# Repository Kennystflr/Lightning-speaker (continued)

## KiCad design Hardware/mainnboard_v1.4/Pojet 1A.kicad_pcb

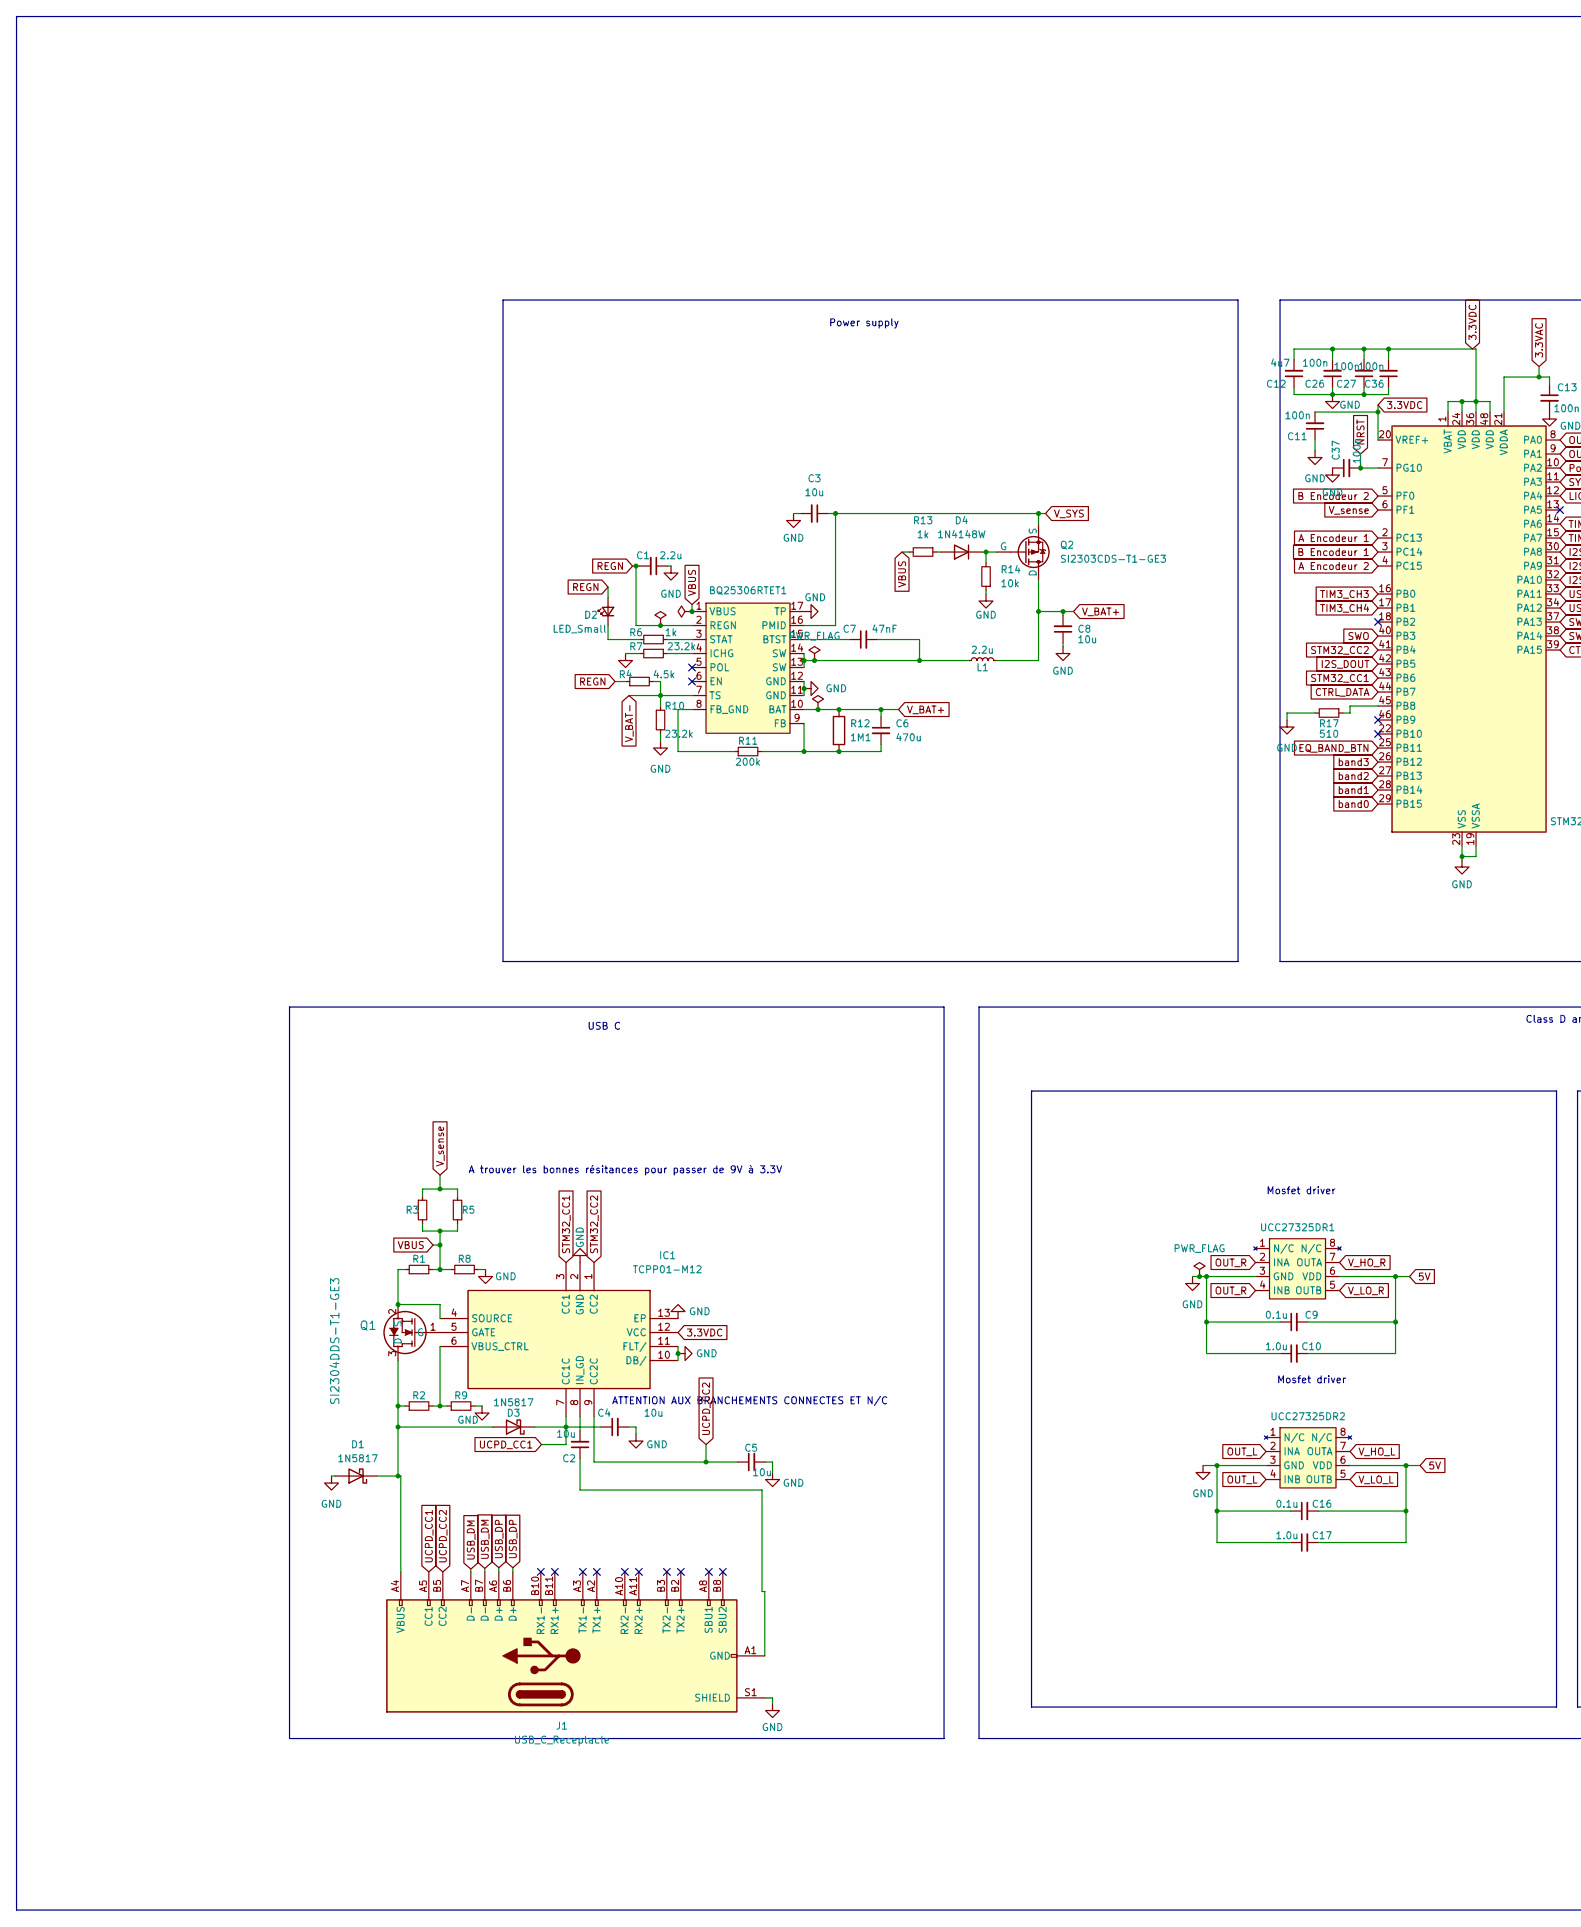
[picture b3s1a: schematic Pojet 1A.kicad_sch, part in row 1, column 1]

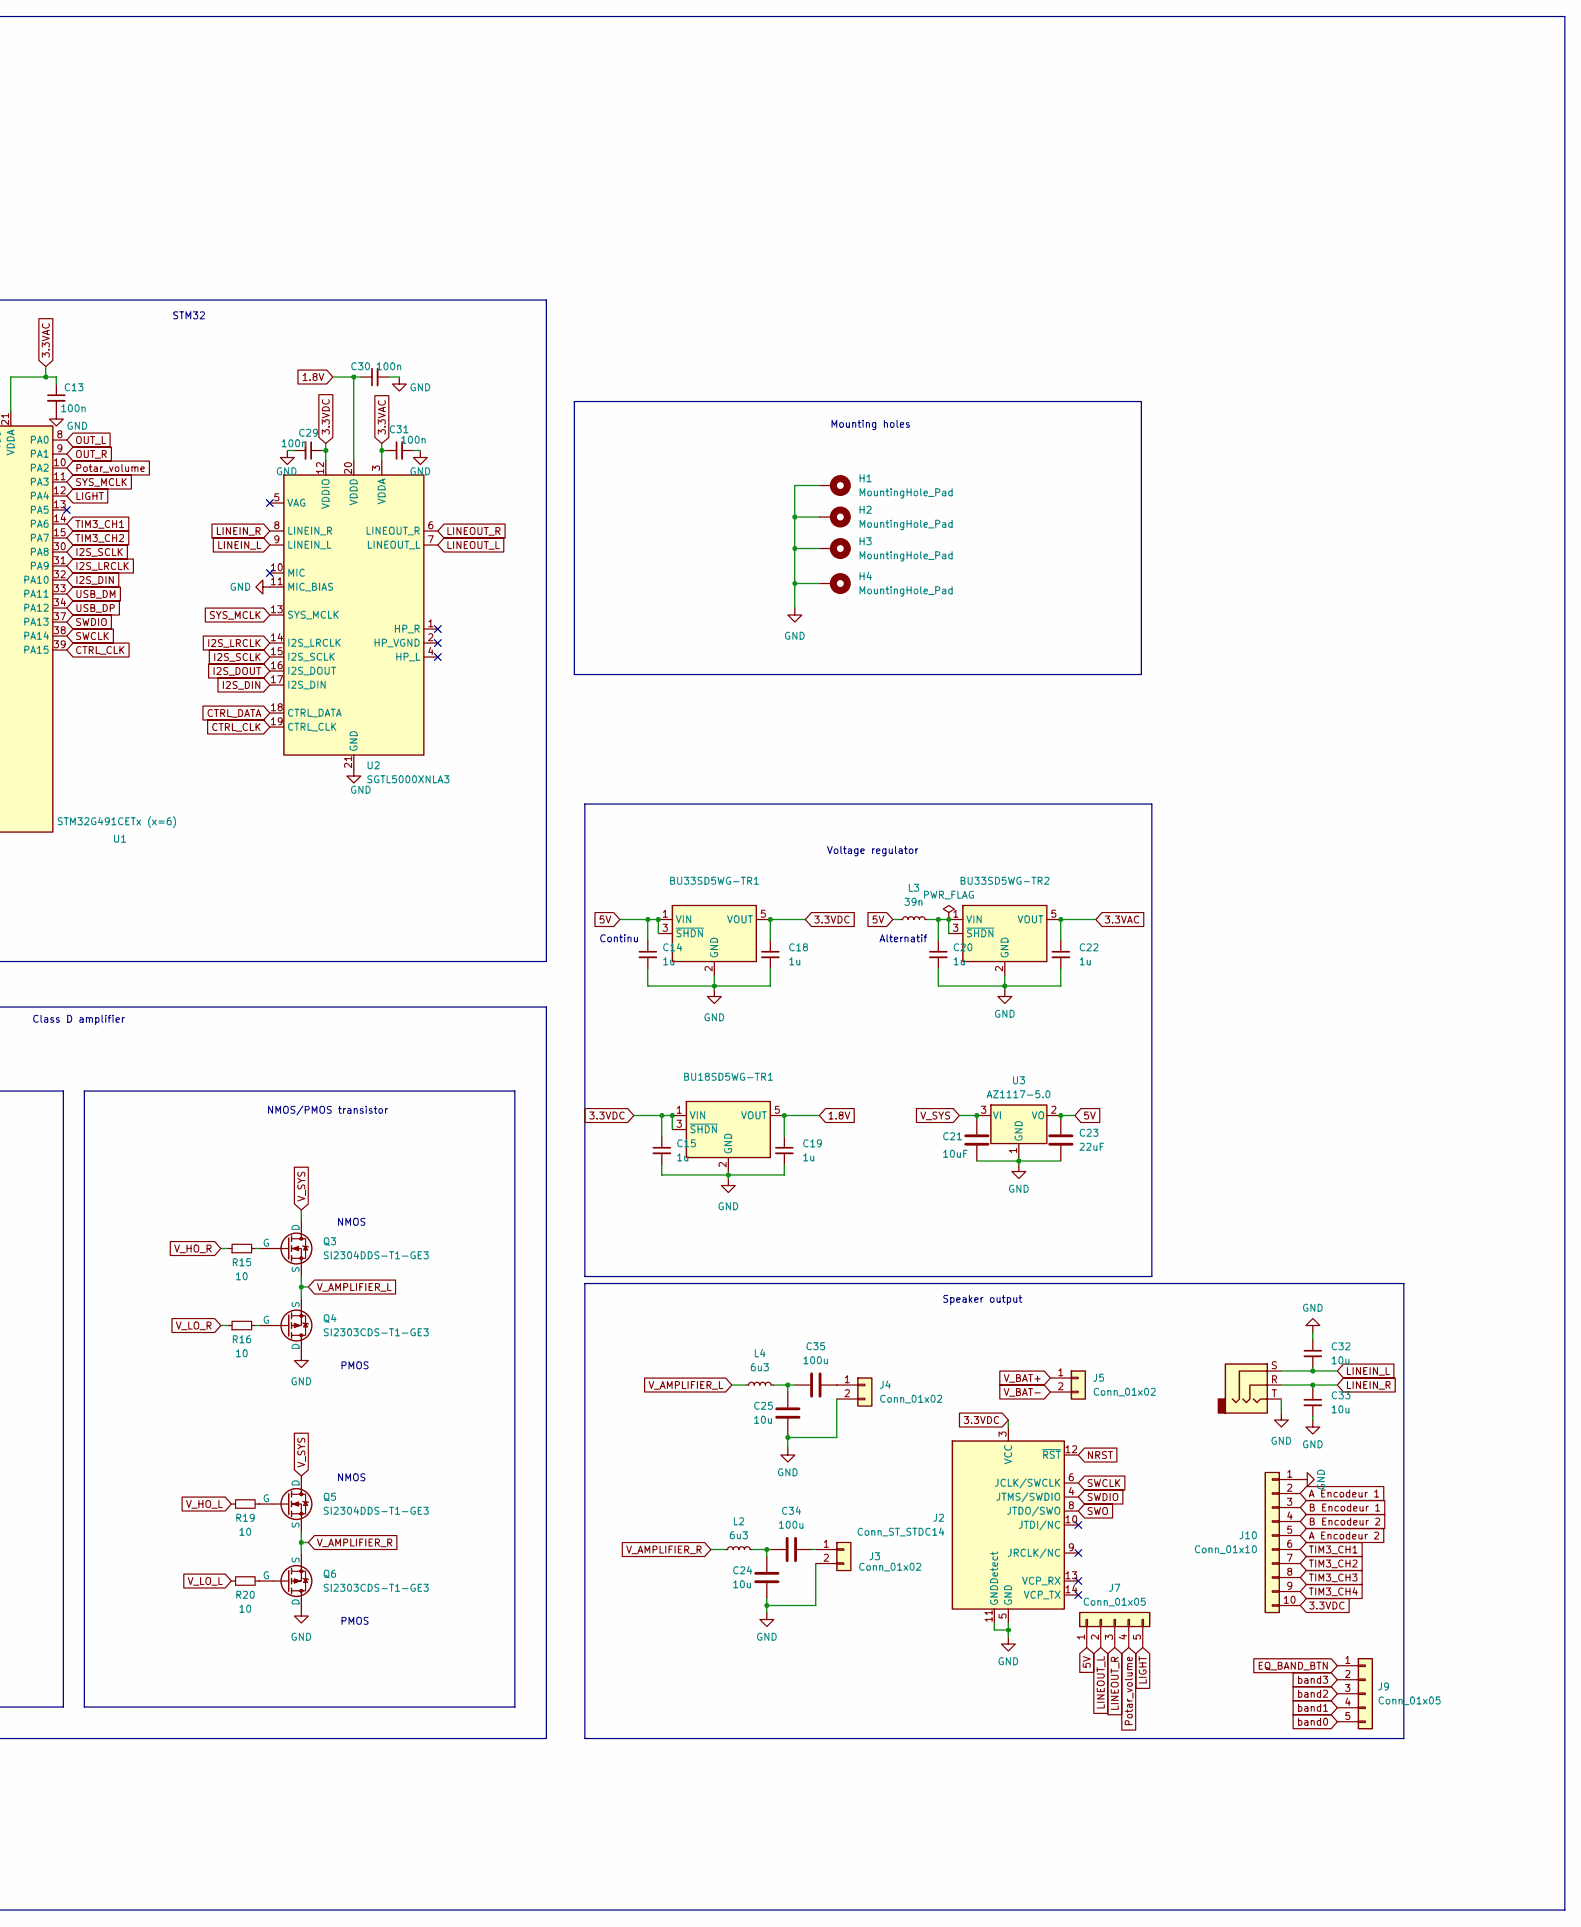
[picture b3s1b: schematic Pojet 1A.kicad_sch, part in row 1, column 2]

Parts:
BQ25306RTET1: WQFN-16-1EP_3x3mm_P0.5mm_EP1.75x1.75mm
BU18SD5WG-TR1, BU33SD5WG-TR1, BU33SD5WG-TR2: LM1117DT-3.3; SOT-23-5
C1: 2.2u; C_0805_2012Metric_Pad1.18x1.45mm_HandSolder
C2, C3, C4, C5, C8, C24, C25, C32, C33: 10u; C_0805_2012Metric_Pad1.18x1.45mm_HandSolder
C6: 470u; C_0805_2012Metric_Pad1.18x1.45mm_HandSolder
C7: 47nF; C_0805_2012Metric_Pad1.18x1.45mm_HandSolder
C9, C16: 0.1u; C_0805_2012Metric_Pad1.18x1.45mm_HandSolder
C10, C17: 1.0u; C_0805_2012Metric_Pad1.18x1.45mm_HandSolder
C11, C13, C26, C27, C29, C30, C31, C36, C37: 100n; C_0805_2012Metric_Pad1.18x1.45mm_HandSolder
C12: 4u7; C_0805_2012Metric_Pad1.18x1.45mm_HandSolder
C14, C15, C18, C19, C20, C22: 1u; C_0805_2012Metric_Pad1.18x1.45mm_HandSolder
C21: 10uF; C_0805_2012Metric_Pad1.18x1.45mm_HandSolder
C23: 22uF; C_0805_2012Metric_Pad1.18x1.45mm_HandSolder
C34, C35: 100u; C_Radial_D5.0mm_H11.0mm_P2.00mm
D1, D3: 1N5817; D_DO-41_SOD81_P10.16mm_Horizontal
D2: LED_Small; LED_D10.0mm
D4: 1N4148W; D_SOD-123
H1, H2, H3, H4: MountingHole_Pad; MountingHole_3.2mm_M3_DIN965_Pad
IC1: TCPP01-M12; LQFN-12-1EP_2x2mm_P0.5mm_EP0.7x0.7mm; Manufacturer_Part_Number TCPP01-M12; Mouser Part Number 511-TCPP01-M12
J1: USB_C_Receptacle; USB_C_Receptacle_GCT_USB4115-03-C
J2: Conn_ST_STDC14; PinHeader_2x07_P1.27mm_Vertical_SMD
J3, J4, J5: Conn_01x02; JST_XH_B2B-XH-A_1x02_P2.50mm_Vertical
J7, J9: Conn_01x05; PinHeader_1x05_P2.54mm_Vertical
J8: AudioJack3; Jack_6.35mm_Neutrik_NJ3FD-V_Vertical
J10: Conn_01x10; PinHeader_1x10_P2.54mm_Vertical
L1: 2.2u; L_0805_2012Metric_Pad1.05x1.20mm_HandSolder
L2, L4: 6u3; L_Vishay_IFSC-1515AH_4x4x1.8mm
L3: 39n; L_0603_1608Metric_Pad1.05x0.95mm_HandSolder
Q1, Q3, Q5: SI2304DDS-T1-GE3; SOT-23
Q2, Q4, Q6: SI2303CDS-T1-GE3; SOT-23
R1, R2, R3, R5, R8, R9: R_0603_1608Metric_Pad0.98x0.95mm_HandSolder
R4: 4.5k; R_0603_1608Metric_Pad0.98x0.95mm_HandSolder
R6, R13: 1k; R_0603_1608Metric_Pad0.98x0.95mm_HandSolder
R7, R10: 23.2k; R_0603_1608Metric_Pad0.98x0.95mm_HandSolder
R11: 200k; R_0603_1608Metric_Pad0.98x0.95mm_HandSolder
R12: 1M1; R_0603_1608Metric_Pad0.98x0.95mm_HandSolder
R14: 10k; R_0603_1608Metric_Pad0.98x0.95mm_HandSolder
R15, R16, R19, R20: 10; R_0603_1608Metric_Pad0.98x0.95mm_HandSolder
R17: 510; R_0603_1608Metric_Pad0.98x0.95mm_HandSolder
U1: STM32G491CETx (x=6); LQFP-48_7x7mm_P0.5mm
U2: SGTL5000XNLA3; QFN-20-1EP_3x3mm_P0.4mm_EP1.65x1.65mm
U3: AZ1117-5.0; SOT-223-3_TabPin2
UCC27325DR1, UCC27325DR2: SOIC-8_3.9x4.9mm_P1.27mm

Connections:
1.8V: BU18SD5WG-TR1.5 (VOUT), C19.1, C30.1, U2.20 (VDDD)
3.3VAC: BU33SD5WG-TR2.5 (VOUT), C13.1, C22.1, C31.1, U1.21 (VDDA), U2.3 (VDDA)
3.3VDC: BU18SD5WG-TR1.1 (VIN), BU18SD5WG-TR1.3 (~SHDN), BU33SD5WG-TR1.5 (VOUT), C11.2, C12.2, C15.1, C18.1, C26.2, C27.2, C29.1, C36.2, IC1.12 (VCC), J2.3 (VCC), J10.10, U1.1 (VBAT), U1.20 (VREF+), U1.24 (VDD), U1.36 (VDD), U1.48 (VDD), U2.12 (VDDIO)
5V: BU33SD5WG-TR1.1 (VIN), BU33SD5WG-TR1.3 (~SHDN), C9.2, C10.2, C14.1, C16.2, C17.2, C23.1, J7.1, L3.1, U3.2 (VO), UCC27325DR1.6 (VDD), UCC27325DR2.6 (VDD)
A Encodeur 1: J10.2, U1.2 (PC13)
A Encodeur 2: J10.5, U1.4 (PC15)
B Encodeur 1: J10.3, U1.3 (PC14)
B Encodeur 2: J10.4, U1.5 (PF0)
CTRL_CLK: U1.39 (PA15), U2.19 (CTRL_CLK)
CTRL_DATA: U1.44 (PB7), U2.18 (CTRL_DATA)
EQ_BAND_BTN: J9.1, U1.25 (PB11)
GND: BQ25306RTET1.11 (GND), BQ25306RTET1.12 (GND), BQ25306RTET1.17 (TP), BU18SD5WG-TR1.2 (GND), BU33SD5WG-TR1.2 (GND), BU33SD5WG-TR2.2 (GND), C1.1, C3.2, C4.2, C5.2, C8.1, C9.1, C10.1, C11.1, C12.1, C13.2, C14.2, C15.2, C16.1, C17.1, C18.2, C19.2, C20.2, C21.2, C22.2, C23.2, C24.2, C25.2, C26.1, C27.1, C29.2, C30.2, C31.2, C32.1, C33.2, C36.1, C37.1, D1.2 (A), H1.1, H2.1, H3.1, H4.1, IC1.2 (GND), IC1.10 (DB/), IC1.11 (FLT/), IC1.13 (EP), J1.S1 (SHIELD), J2.5 (GND), J2.7 (GND), J2.11 (GNDDetect), J3.2, J4.2, J8.T, J10.1, Q4.1 (D), Q6.1 (D), R7.2, R8.2, R9.2, R10.2, R14.1, R17.2, U1.19 (VSSA), U1.23 (VSS), U1.35 (VSS), U1.47 (VSS), U2.11 (MIC_BIAS), U2.21 (GND), U3.1 (GND), UCC27325DR1.3 (GND), UCC27325DR2.3 (GND)
I2S_DIN: U1.32 (PA10), U2.17 (I2S_DIN)
I2S_DOUT: U1.42 (PB5), U2.16 (I2S_DOUT)
I2S_LRCLK: U1.31 (PA9), U2.14 (I2S_LRCLK)
I2S_SCLK: U1.30 (PA8), U2.15 (I2S_SCLK)
LIGHT: J7.5, U1.12 (PA4)
LINEIN_L: C32.2, J8.S, U2.9 (LINEIN_L)
LINEIN_R: C33.1, J8.R, U2.8 (LINEIN_R)
LINEOUT_L: J7.2, U2.7 (LINEOUT_L)
LINEOUT_R: J7.3, U2.6 (LINEOUT_R)
NRST: C37.2, J2.12 (~RST), U1.7 (PG10)
unnamed: BQ25306RTET1.15 (BTST), C7.1
unnamed: BQ25306RTET1.9 (FB), C6.2, R11.2, R12.2
unnamed: BQ25306RTET1.8 (FB_GND), R11.1
unnamed: BQ25306RTET1.4 (ICHG), R7.1
unnamed: BQ25306RTET1.3 (STAT), R6.1
unnamed: BQ25306RTET1.13 (SW), BQ25306RTET1.14 (SW), C7.2, L1.1
unnamed: BU33SD5WG-TR2.1 (VIN), BU33SD5WG-TR2.3 (~SHDN), C20.1, L3.2
unnamed: C2.1, J1.A1 (GND), J1.A12 (GND), J1.B1 (GND), J1.B12 (GND)
unnamed: C24.1, C34.1, L2.2
unnamed: C25.1, C35.1, L4.2
unnamed: D1.1 (K), D3.2 (A), J1.A4 (VBUS), J1.A9 (VBUS), J1.B4 (VBUS), J1.B9 (VBUS), Q1.3 (D), R2.1
unnamed: D2.1 (K), R6.2
unnamed: D4.2 (A), R13.1
unnamed: D4.1 (K), Q2.2 (G), R14.2
unnamed: IC1.5 (GATE), Q1.1 (G)
unnamed: C2.2, IC1.8 (IN_GD)
unnamed: IC1.4 (SOURCE), Q1.2 (S), R1.1
unnamed: IC1.6 (VBUS_CTRL), R2.2, R9.1
unnamed: C34.2, J3.1
unnamed: C35.2, J4.1
unnamed: Q3.2 (G), R15.2
unnamed: Q4.2 (G), R16.2
unnamed: Q5.2 (G), R19.2
unnamed: Q6.2 (G), R20.2
unnamed: R17.1, U1.45 (PB8)
OUT_L: U1.8 (PA0), UCC27325DR2.2 (INA), UCC27325DR2.4 (INB)
OUT_R: U1.9 (PA1), UCC27325DR1.2 (INA), UCC27325DR1.4 (INB)
Potar_volume: J7.4, U1.10 (PA2)
REGN: BQ25306RTET1.2 (REGN), C1.2, D2.2 (A), R4.1
STM32_CC1: IC1.3 (CC1), U1.43 (PB6)
STM32_CC2: IC1.1 (CC2), U1.41 (PB4)
SWCLK: J2.6 (JCLK/SWCLK), U1.38 (PA14)
SWDIO: J2.4 (JTMS/SWDIO), U1.37 (PA13)
SWO: J2.8 (JTDO/SWO), U1.40 (PB3)
SYS_MCLK: U1.11 (PA3), U2.13 (SYS_MCLK)
TIM3_CH1: J10.6, U1.14 (PA6)
TIM3_CH2: J10.7, U1.15 (PA7)
TIM3_CH3: J10.8, U1.16 (PB0)
TIM3_CH4: J10.9, U1.17 (PB1)
UCPD_CC1: C4.1, D3.1 (K), IC1.7 (CC1C), J1.A5 (CC1)
UCPD_CC2: C5.1, IC1.9 (CC2C), J1.B5 (CC2)
USB_DM: J1.A7 (D-), J1.B7 (D-), U1.33 (PA11)
USB_DP: J1.A6 (D+), J1.B6 (D+), U1.34 (PA12)
VBUS: BQ25306RTET1.1 (VBUS), R1.2, R3.2, R5.2, R8.1, R13.2
V_AMPLIFIER_L: L4.1, Q3.3 (S), Q4.3 (S)
V_AMPLIFIER_R: L2.1, Q5.3 (S), Q6.3 (S)
V_BAT+: BQ25306RTET1.10 (BAT), C6.1, C8.2, J5.1, L1.2, Q2.1 (D), R12.1
V_BAT-: BQ25306RTET1.7 (TS), J5.2, R4.2, R10.1
V_HO_L: R19.1, UCC27325DR2.7 (OUTA)
V_HO_R: R15.1, UCC27325DR1.7 (OUTA)
V_LO_L: R20.1, UCC27325DR2.5 (OUTB)
V_LO_R: R16.1, UCC27325DR1.5 (OUTB)
V_SYS: BQ25306RTET1.16 (PMID), C3.1, C21.1, Q2.3 (S), Q3.1 (D), Q5.1 (D), U3.3 (VI)
V_sense: R3.1, R5.1, U1.6 (PF1)
band0: J9.5, U1.29 (PB15)
band1: J9.4, U1.28 (PB14)
band2: J9.3, U1.27 (PB13)
band3: J9.2, U1.26 (PB12)

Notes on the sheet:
Speaker output
A trouver les bonnes résitances pour passer de 9V à 3.3V
PMOS
NMOS
ATTENTION AUX BRANCHEMENTS CONNECTES ET N/C
NMOS/PMOS transistor
Continu
Mounting holes
Voltage regulator
USB C
Alternatif
Mosfet driver
STM32
Class D amplifier
Power supply

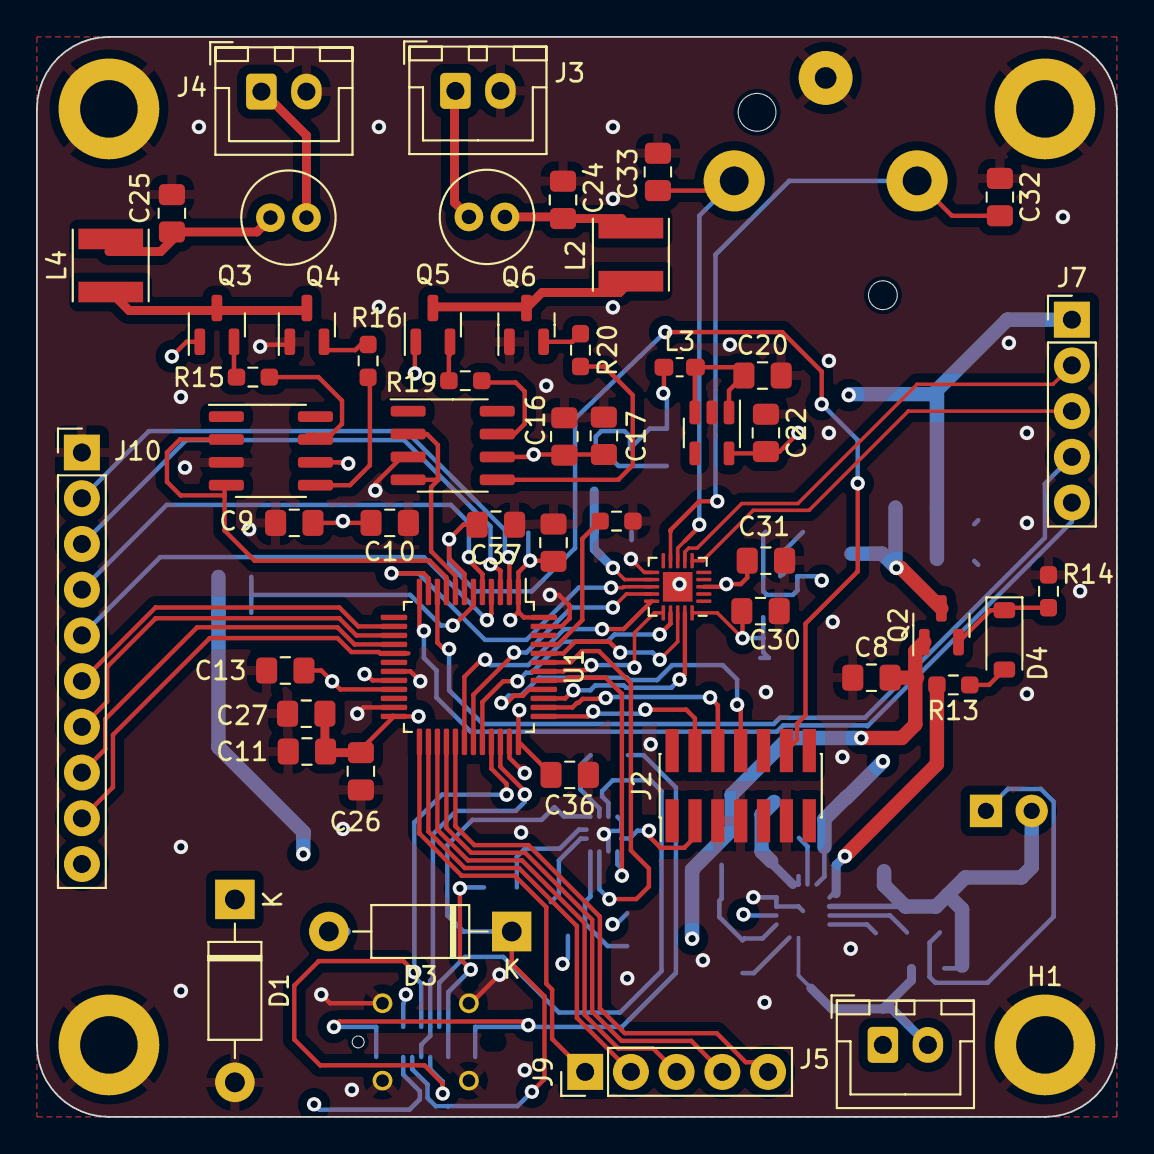
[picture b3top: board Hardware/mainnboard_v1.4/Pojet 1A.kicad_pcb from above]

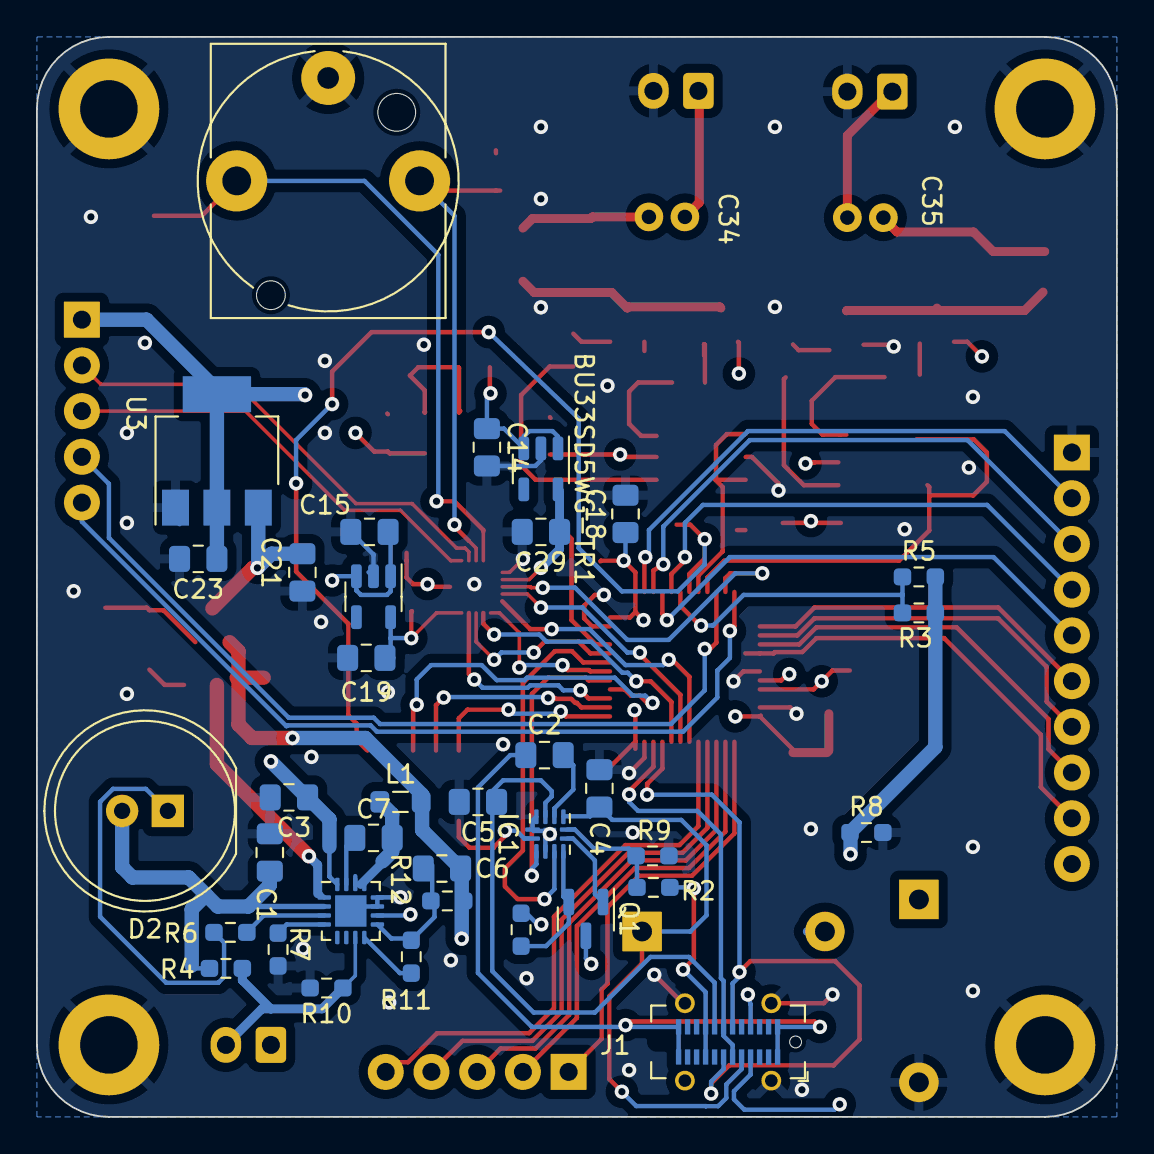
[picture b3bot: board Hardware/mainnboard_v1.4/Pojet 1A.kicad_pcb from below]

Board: 4 copper layers, 60.0 x 60.0 mm, 92 parts (36 on the bottom side), 80 nets.

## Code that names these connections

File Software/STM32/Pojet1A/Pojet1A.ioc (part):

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Mcu.Name=STM32G491C(C-E)Tx
Mcu.Package=LQFP48
Mcu.UserName=STM32G491CETx
PA0.GPIOParameters=GPIO_Label
PA0.GPIO_Label=Out_L
PA0.Signal=S_TIM2_CH1
PA1.GPIOParameters=GPIO_Label
PA1.GPIO_Label=Out_R
PA1.Signal=S_TIM2_CH2
PA10.Mode=SAI_A_MasterWithClock
PA10.Signal=SAI1_SD_A
PA11.Mode=Device
PA11.Signal=USB_DM
PA12.Mode=Device
PA12.Signal=USB_DP
PA13.Mode=Trace_Asynchronous_SW
PA13.Signal=SYS_JTMS-SWDIO
PA14.Mode=Trace_Asynchronous_SW
PA14.Signal=SYS_JTCK-SWCLK
PA15.Mode=I2C
PA15.Signal=I2C1_SCL
PA2.GPIOParameters=GPIO_Label
PA2.GPIO_Label=pot_volume
PA2.Mode=IN3-Single-Ended
PA2.Signal=ADC1_IN3
PA3.Mode=SAI_A_MasterWithClock
PA3.Signal=SAI1_MCLK_A
PA4.GPIOParameters=GPIO_Label
PA4.GPIO_Label=light
PA4.Signal=GPIO_Output
PA6.Signal=S_TIM3_CH1
PA7.Signal=S_TIM3_CH2
PA8.Mode=SAI_A_MasterWithClock
PA8.Signal=SAI1_SCK_A
PA9.Mode=SAI_A_MasterWithClock
PA9.Signal=SAI1_FS_A
PB0.Signal=S_TIM3_CH3
PB1.Signal=S_TIM3_CH4
PB10.Mode=Asynchronous
PB10.Signal=USART3_TX
PB11.GPIOParameters=GPIO_Label,GPIO_ModeDefaultEXTI
PB11.GPIO_Label=eq_band_btn
PB11.GPIO_ModeDefaultEXTI=GPIO_MODE_IT_RISING
PB11.Signal=GPXTI11
PB12.GPIOParameters=GPIO_Label
PB12.GPIO_Label=band3
PB12.Signal=GPIO_Output
PB13.GPIOParameters=GPIO_Label
PB13.GPIO_Label=band2
PB13.Signal=GPIO_Output
PB14.GPIOParameters=GPIO_Label
PB14.GPIO_Label=band1
PB14.Signal=GPIO_Output
PB15.GPIOParameters=GPIO_Label
PB15.GPIO_Label=band0
PB15.Signal=GPIO_Output
PB3.Mode=Trace_Asynchronous_SW
PB3.Signal=SYS_JTDO-SWO
PB4.Mode=Sink_AllSignals
PB4.Signal=UCPD1_CC2
PB5.Mode=SAI_B_SyncSlave
PB5.Signal=SAI1_SD_B
PB6.Mode=Sink_AllSignals
PB6.Signal=UCPD1_CC1
PB7.Mode=I2C
PB7.Signal=I2C1_SDA
PB8-BOOT0.Mode=Asynchronous
PB8-BOOT0.Signal=USART3_RX
PC13.GPIOParameters=GPIO_Label,GPIO_ModeDefaultEXTI
PC13.GPIO_Label=A1
PC13.GPIO_ModeDefaultEXTI=GPIO_MODE_IT_RISING_FALLING
PC13.Signal=GPXTI13
PC14-OSC32_IN.GPIOParameters=GPIO_Label,GPIO_ModeDefaultEXTI
PC14-OSC32_IN.GPIO_Label=A2
PC14-OSC32_IN.GPIO_ModeDefaultEXTI=GPIO_MODE_IT_RISING_FALLING
PC14-OSC32_IN.Signal=GPXTI14
PC15-OSC32_OUT.GPIOParameters=GPIO_Label,GPIO_ModeDefaultEXTI
PC15-OSC32_OUT.GPIO_Label=B1
PC15-OSC32_OUT.GPIO_ModeDefaultEXTI=GPIO_MODE_IT_RISING_FALLING
PC15-OSC32_OUT.Signal=GPXTI15
PF0-OSC_IN.GPIOParameters=GPIO_Label,GPIO_ModeDefaultEXTI
PF0-OSC_IN.GPIO_Label=B2
PF0-OSC_IN.GPIO_ModeDefaultEXTI=GPIO_MODE_IT_RISING_FALLING
PF0-OSC_IN.Signal=GPXTI0
PF1-OSC_OUT.GPIOParameters=GPIO_Label
PF1-OSC_OUT.GPIO_Label=V_sense
PF1-OSC_OUT.Mode=IN10-Single-Ended
PF1-OSC_OUT.Signal=ADC2_IN10
RCC.HSE_VALUE=8000000
RCC.SYSCLKFreq_VALUE=16000000
board=custom

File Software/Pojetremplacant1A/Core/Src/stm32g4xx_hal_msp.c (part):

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
    __HAL_RCC_GPIOB_CLK_ENABLE();
    /**ADC1 GPIO Configuration
    PB0     ------> ADC1_IN15
    */
    GPIO_InitStruct.Pin = GPIO_PIN_0;
    GPIO_InitStruct.Mode = GPIO_MODE_ANALOG;
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    __HAL_RCC_ADC12_CLK_DISABLE();

    /**ADC1 GPIO Configuration
    PB0     ------> ADC1_IN15
    */
    HAL_GPIO_DeInit(GPIOB, GPIO_PIN_0);

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
    __HAL_RCC_GPIOA_CLK_ENABLE();
    /**TIM3 GPIO Configuration
    PA6     ------> TIM3_CH1
    PA7     ------> TIM3_CH2
    */
    GPIO_InitStruct.Pin = GPIO_PIN_6|GPIO_PIN_7;
    GPIO_InitStruct.Mode = GPIO_MODE_AF_PP;
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
    __HAL_RCC_GPIOA_CLK_ENABLE();
    /**USART2 GPIO Configuration
    PA2     ------> USART2_TX
    PA3     ------> USART2_RX
    */
    GPIO_InitStruct.Pin = USART2_TX_Pin|USART2_RX_Pin;
    GPIO_InitStruct.Mode = GPIO_MODE_AF_PP;
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    __HAL_RCC_USART2_CLK_DISABLE();

    /**USART2 GPIO Configuration
    PA2     ------> USART2_TX
    PA3     ------> USART2_RX
    */
    HAL_GPIO_DeInit(GPIOA, USART2_TX_Pin|USART2_RX_Pin);

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
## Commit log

2024-02-26 Create 1st.txt
    a nonsense
2024-02-26 Create Firmware
2024-02-26 Rename Code/CodeSlashlebest.py to Code2
2024-02-26 Delete LICENSE
    Pas besoin
2024-02-26 Create Test
2024-02-26 Schema de l'ampli class D
2024-02-26 Create datasheet
2024-02-26 Create Spécifications
2024-02-27 Update ToBuy.txt
    MOSFET Driver et USB C power Delivery IC
2024-02-27 Update oldnotes.txt
    Work in progress... le fichier sera une description succincte mais immersive du système.
2024-02-27 Rename ToBuy.txt to Hardware/ToBuy.txt
2024-02-27 Update and rename oldnotes.txt to reviewedNotes.txt
    Notes détaillants les sous-systèmes du projet
2024-03-02 update schematic ampli
2024-03-02 uploaded schematic v2
2024-03-02 updated amplifier schematic v3
2024-03-03 Add files via upload
    ir2184
2024-03-03 Create yes
2024-03-04 Rename projects6_1.png to projectLS v1.2.png
2024-03-05 Rename Hardware/SchémanSTM32p132.PNG to Hardware/ADC_Potentiometres/SchémaSTM32p132.PNG
2024-03-05 Rename SchémaSTM32p132.PNG to SchémaSTM32p132.PNG
2024-03-05 Rename reqs.txt to reqs.docx
2024-03-05 Rename reqs.docx to reqs.txt
2024-03-05 Rename Software/STM32/STM32G431KBTX_FLASH.ld to Software/STM32/CubeIDEpj/STM32G431KBTX_FLASH.ld
2024-03-05 Projet CubeIDE implémentation des IOs
2024-03-11 Create test1
2024-03-11 Create Test2
2024-03-11 Create Test3
2024-03-11 Delete datasheets/Transistor Mos IRF640.PDF
    Pas besoin de ce Mos
2024-03-11 Create TEst4
2024-03-11 Create TEst5
2024-03-11 Add files via upload
    Le Mosfet Driver d'origine
2024-03-11 Create code c mise sur 128 valeurs
2024-03-11 Update code c mise sur 128 valeurs
2024-03-11 Create BQ25306
2024-03-11 BQ25306
2024-03-11 Create STM32G491KBT6
2024-03-11 ampli v4
2024-03-18 protection electrostatique
2024-03-18 Rename Circuit-Diagram-of-Transistorized-Class-D-Power-Amplifier-Half-Bridge-Configuration-02.jpg to Hardware/Circuit-Diagram-of-Transistorized-Class-D-Power-Amplifier-Half-Bridge-Configuration-02.jpg
2024-03-18 Ampli v5
2024-03-18 Create code en cours pr la modificatino de la valeur par la roue
2024-03-25 Rename Software/modif_sgtl.c to Software/STM32/modif_sgtl.c
2024-03-25 filter eq
    fonctions qui effectuent une équalisation
2024-03-25 Ampli v6
2024-03-25 Rename TEst to TEst
2024-03-25 Rename dm00312034-1798874.pdf to dm00312034-1798874.pdf
2024-03-28 stm32 modifs
2024-03-30 apli v7
2024-04-04 mainboard 1.1 in progress
    editing capacity values and adding of the STM32 programing connector
2024-04-04 new relase of the board
2024-04-05 Add files via upload
    DE
2024-04-05 Create hey.md
    creating the repository
2024-04-05 PCB avec les vias traversants
2024-04-05 hey
    update
2024-04-05 Add files via upload
    update 1 error
2024-04-29 Secondary Board v1 Schematic
2024-04-29 library
2024-04-29 Updated STM 32
2024-04-29 update pff
2024-04-29 explicit name
2024-04-29 PCB update still some errors
2024-04-30 It's good few mistakes but not real ones,
2024-04-30 Edit
    Remise en cohérence du placement de certains composants(R C) pas grands chose d'importants
2024-05-03 Finished Update
2024-05-06 little vias edit and gerber plot
2024-05-06 Adding gerber files
2024-05-07 last gerber vias and track size edits
2024-05-13 Yello
2024-05-23 Final edit for building conformity
2024-05-23 new version not finised
2024-05-24 Stable with filters and leds Handling
    Sorry for the 7z format I had no choice file was too big
2024-05-27 Encoder datasheet
2024-05-27 Rename datasheets/encoders-12CE-datasheet.pdf to datasheets/encoder/encoders-12CE-datasheet.pdf
2024-06-03 Rename Software/STM32/testPj1.1.zip to Software/STM32/Old/testPj1.1.zip
2024-06-03 final sorting
2024-06-03 sorting
2024-06-03 Rename projectLS v1.2.png to Hardware/Old/projectLS v1.2.png
2024-06-03 Rename reviewedNotes.txt to Hardware/Old/reviewedNotes.txt
